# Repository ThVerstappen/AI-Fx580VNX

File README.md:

# AI-Fx580VNX

Bo mạch thay thế cho Casio fx-580VN X (ESP32-S3, TCA8418, e-paper 2,13", USB-C, pin LiPo). Đây là phần hoàn thiện nhất: **V8 USB_FIX1** (11/10/2026).

- `Hardware/FX580_Main_EPD_LAYOUT_V8/` — project KiCad 10.0.5 (sch/pcb/lib local, BOM/CPL, báo cáo ERC/DRC/CAM). Đọc `USB_FIX1_REPORTS/REVIEW_USB_FIX1.md` trước.
- `GOI_GERBER_FX580_V8_USB_FIX1_5PCB/` — Gerber/Excellon cho 5 PCB trống.
- `GOI_LAP_6_LINH_KIEN_FX580_V8_USB_FIX1_2BO/` — BOM/CPL lắp 6 linh kiện.
- `GOI_STENCIL_FX580_V8_USB_FIX1_65PARTS/` — stencil 65 linh kiện còn lại.
- `HUONG_DAN_SETUP_MURATA_FX580_V8/` — hướng dẫn đặt PCB/stencil.

Giới hạn: ERC/DRC = 0 nhưng chưa thử USB/ESD trên bo thật; toàn tuyến 90 Ω chưa được chứng minh. Chưa có firmware hoàn chỉnh. Các phiên bản V2–V7, trial và dữ liệu trung gian không đưa lên.

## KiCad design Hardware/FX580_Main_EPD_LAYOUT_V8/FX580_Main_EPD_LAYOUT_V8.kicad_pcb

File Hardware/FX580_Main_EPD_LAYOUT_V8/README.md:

# FX580 V8 USB_FIX1 — project hiện hành

Revision mới nhất hoàn tất ngày 11/10/2026. Mở **FX580_Main_EPD_LAYOUT_V8.kicad_pro** bằng KiCad 10.0.5; PCB và schematic cùng tên. Thư viện local dùng `${KIPRJMOD}/lib`.

Đã sửa routing D−/D+, cải thiện GND tham chiếu và thêm tụ C25 gần U6. ERC/DRC/unconnected/parity đều 0 theo rules hiện hành. CAM độc lập xác nhận 263 lỗ/slot, pad và 100 miền tiếp điểm của 50 phím. Chi tiết và giới hạn tại **USB_FIX1_REPORTS/REVIEW_USB_FIX1.md**; toàn tuyến 90 Ω và thử USB/ESD trên bo thật vẫn cần xác nhận.

BOM/CPL hiện hành: `assembly/BOM_JLCPCB_V8_USB_FIX1.csv` và `assembly/CPL_JLCPCB_V8_USB_FIX1.csv`, 35 nhóm / 71 linh kiện mỗi bo. `assembly/inherited_v7/` giữ chứng cứ vị trí/góc/cực của linh kiện không đổi; BOM V7 không bao gồm C25.

Gói Gerber mới trong workspace: `GOI_GERBER_FX580_V8_USB_FIX1_5PCB/FX580_V8_USB_FIX1_GERBER.zip`. Phạm vi 5 PCB trống / 0 PCBA / không stencil. Upload/quote JLCONE cũ chưa được thay trong lượt này.

V7 BOOST2 và V8 ngày 08/10 được giữ làm lịch sử. Project trước sửa nằm trong `usb_fix_20261010/V8_BEFORE_USB_FIX1.zip`; assembly cũ tại `usb_fix_20261010/assembly_before_usb/`. Ba file CAD ở root là bản hiện hành; `MANIFEST_SHA256.json` ghi hash các file giao. Bản ZIP project có đủ thư viện, BOM/CPL và báo cáo, không gồm các candidate/trial.

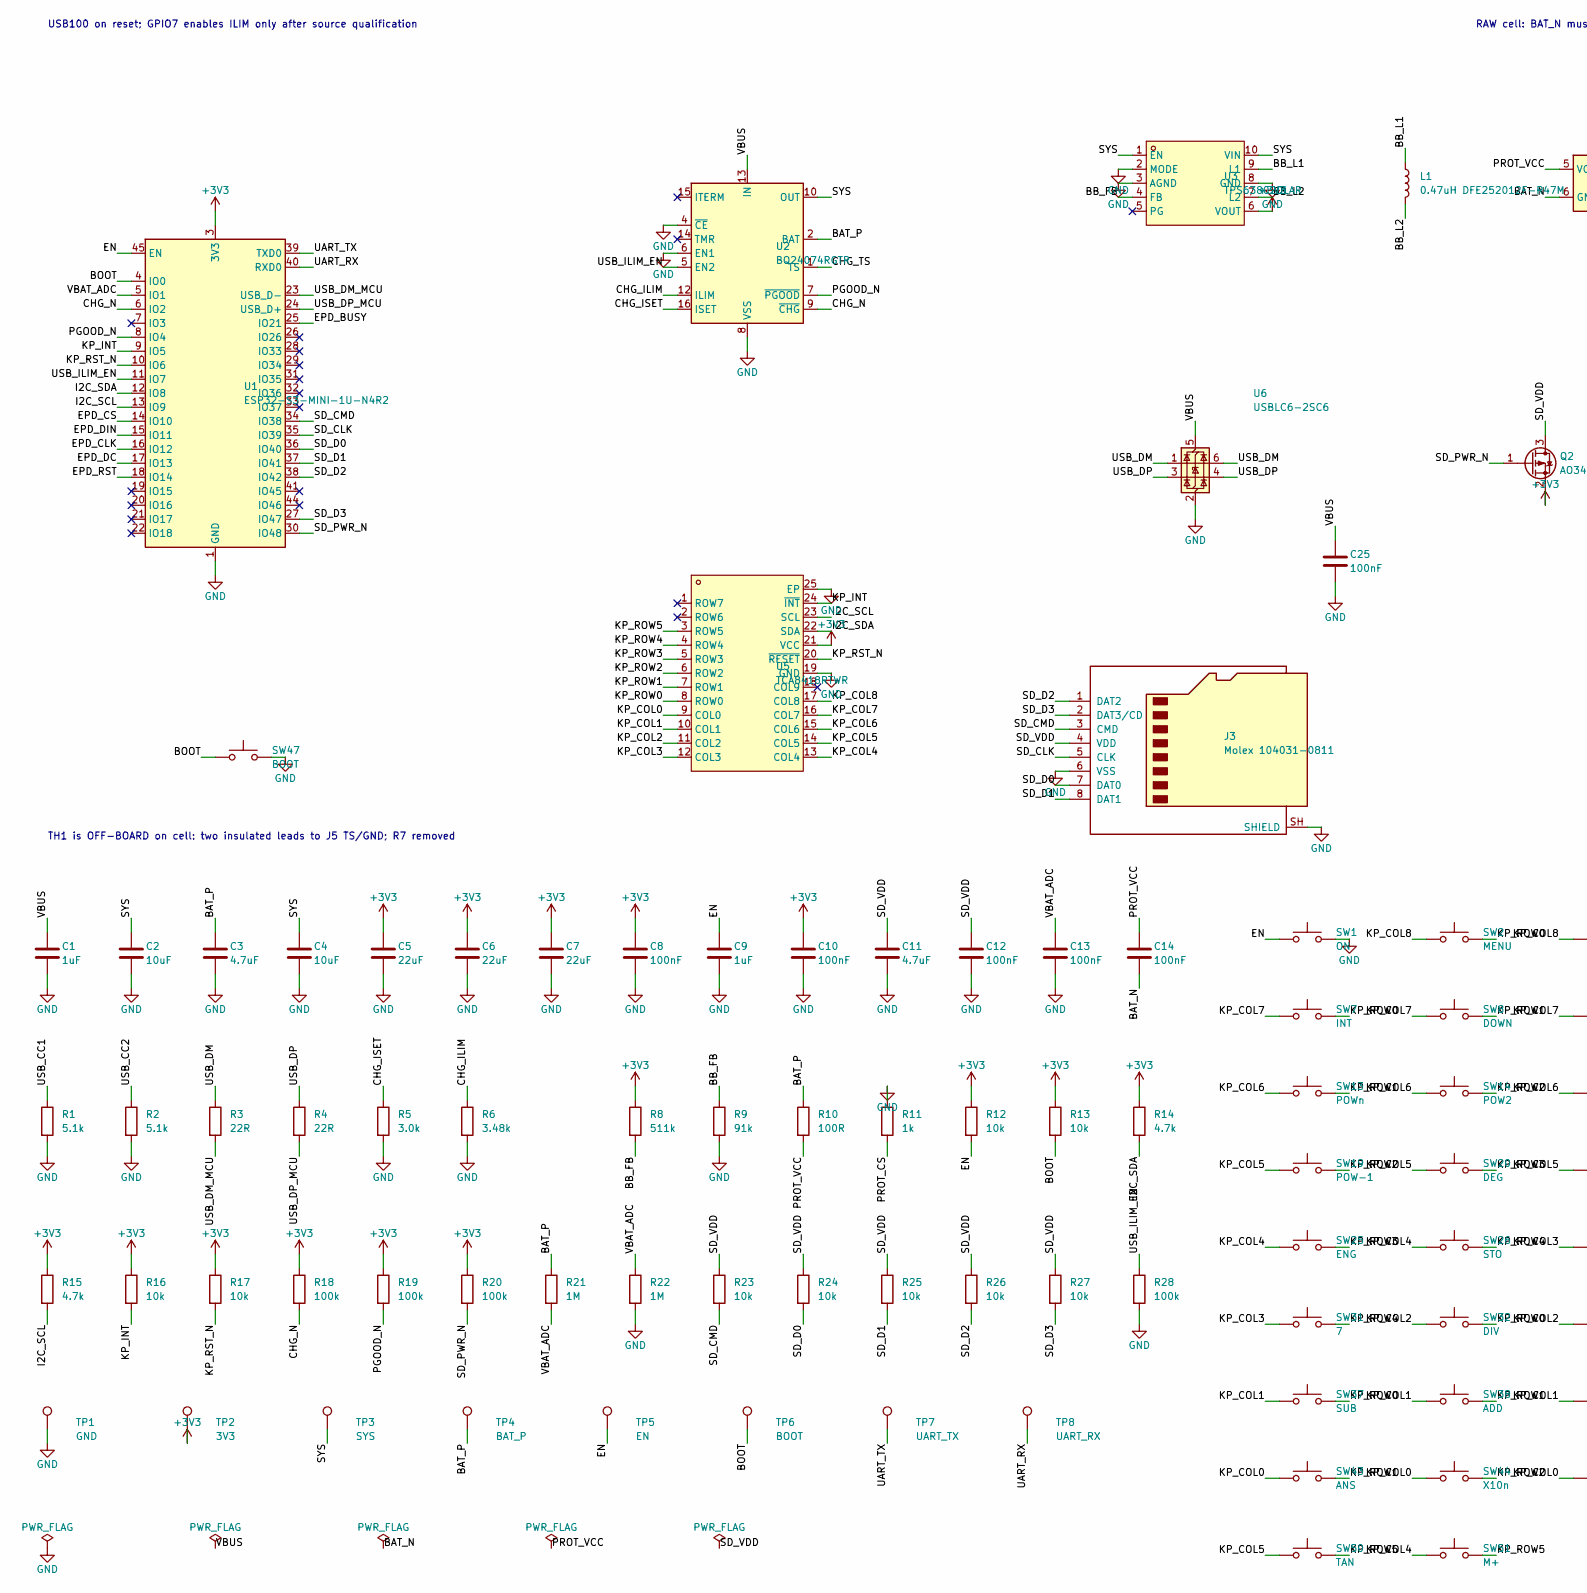
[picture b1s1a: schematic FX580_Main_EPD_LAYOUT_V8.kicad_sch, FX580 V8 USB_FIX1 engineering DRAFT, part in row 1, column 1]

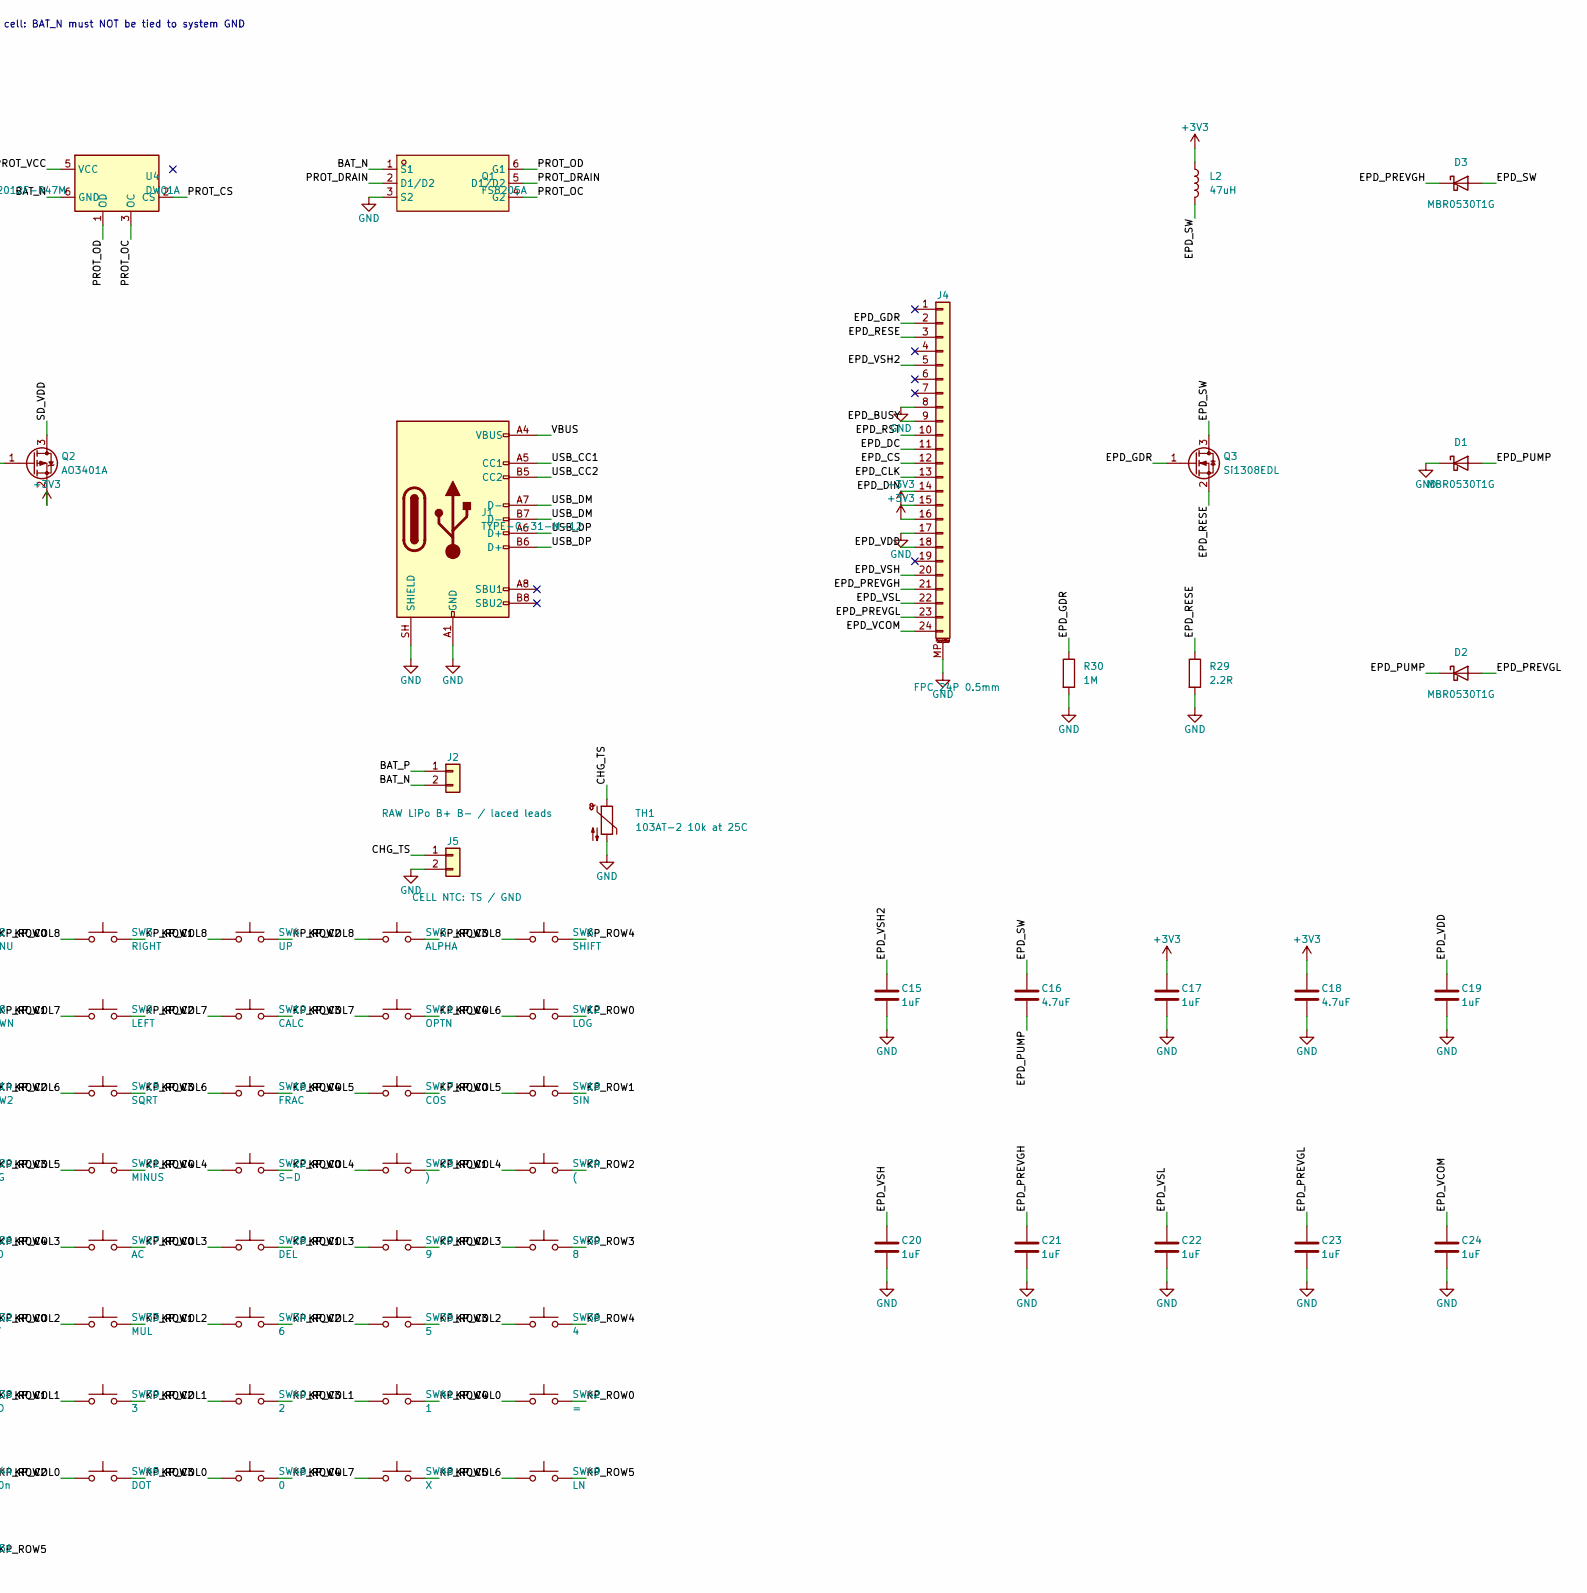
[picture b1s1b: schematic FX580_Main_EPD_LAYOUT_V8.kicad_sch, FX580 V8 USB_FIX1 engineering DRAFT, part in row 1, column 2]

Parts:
C1, C9: 1uF; C_0603_1608Metric; Voltage 50V; LCSC C15849
C2, C4: 10uF; C_0805_2012Metric; Voltage 10V; LCSC C5137471
C3, C11: 4.7uF; C_0603_1608Metric; Voltage 16V; LCSC C19666
C5, C6, C7: 22uF; C_0805_2012Metric; Voltage 10V; LCSC C22367831
C8, C10, C12, C13, C14, C25: 100nF; C_0603_1608Metric; Voltage 50V; LCSC C14663
C15, C17, C19, C20, C21, C22, C23, C24: 1uF; C_0603_1608Metric; Voltage 50V
C16, C18: 4.7uF; C_0805_2012Metric; Voltage 50V
D1, D2, D3: MBR0530T1G; D_SOD-123; MPN MBR0530T1G; LCSC C82046
J1: TYPE-C-31-M-12; USB_C_Receptacle_HRO_TYPE-C-31-M-12; MPN TYPE-C-31-M-12
J2: RAW LiPo B+ B- / laced leads; Battery_Pads_Reinforced
J3: Molex 104031-0811; microSD_HC_Molex_104031-0811; LCSC C585350
J4: FPC 24P 0.5mm; Hirose_FH12-24S-0.5SH_1x24-1MP_P0.50mm_Horizontal; MPN FH12-24S-0.5SH(55)
J5: CELL NTC: TS / GND; Cell_NTC_Pads
L1: 0.47uH DFE252012F-R47M; DFE252012F; LCSC C703140
L2: 47uH; L_TDK_BCL322515RT; MPN BCL322515RT-470M-D; LCSC C3220812
Q1: FS8205A; SOT-23-6_L2.9-W1.6-P0.95-LS2.8-BR; LCSC C2830320
Q2: AO3401A; SOT-23; LCSC C15127
Q3: Si1308EDL; SOT-323_SC-70
R1, R2: 5.1k; R_0603_1608Metric; Tolerance 1%; LCSC C23186
R3, R4: 22R; R_0603_1608Metric; Tolerance 1%; LCSC C23345
R5: 3.0k; R_0603_1608Metric; Tolerance 1%; LCSC C4211
R6: 3.48k; R_0603_1608Metric; Tolerance 1%; LCSC C22996
R8: 511k; R_0603_1608Metric; Tolerance 1%; LCSC C23194
R9: 91k; R_0603_1608Metric; Tolerance 1%; LCSC C23265
R10: 100R; R_0603_1608Metric; Tolerance 1%; LCSC C22775
R11: 1k; R_0603_1608Metric; Tolerance 1%; LCSC C21190
R12, R13, R16, R17, R23, R24, R25, R26, R27: 10k; R_0603_1608Metric; Tolerance 1%; LCSC C2906982
R14, R15: 4.7k; R_0603_1608Metric; Tolerance 1%; LCSC C23162
R18, R19, R20, R28: 100k; R_0603_1608Metric; Tolerance 1%; LCSC C25803
R21, R22: 1M; R_0603_1608Metric; Tolerance 1%; LCSC C22935
R29: 2.2R; R_0603_1608Metric; Tolerance 1%
R30: 1M; R_0603_1608Metric
SW1: ON; Keypad_Interleaved_5p2
SW2: MENU; Keypad_Interleaved_5p2
SW3: RIGHT; Keypad_Interleaved_5p2
SW4: UP; Keypad_Interleaved_5p2
SW5: ALPHA; Keypad_Interleaved_5p2
SW6: SHIFT; Keypad_Interleaved_5p2
SW7: INT; Keypad_Interleaved_5p2
SW8: DOWN; Keypad_Interleaved_5p2
SW9: LEFT; Keypad_Interleaved_5p2
SW10: CALC; Keypad_Interleaved_5p2
SW11: OPTN; Keypad_Interleaved_5p2
SW12: LOG; Keypad_Interleaved_5p2
SW13: POWn; Keypad_Interleaved_5p2
SW14: POW2; Keypad_Interleaved_5p2
SW15: SQRT; Keypad_Interleaved_5p2
SW16: FRAC; Keypad_Interleaved_5p2
SW17: COS; Keypad_Interleaved_5p2
SW18: SIN; Keypad_Interleaved_5p2
SW19: POW-1; Keypad_Interleaved_5p2
SW20: DEG; Keypad_Interleaved_5p2
SW21: MINUS; Keypad_Interleaved_5p2
SW22: S-D; Keypad_Interleaved_5p2
SW23: ); Keypad_Interleaved_5p2
SW24: (; Keypad_Interleaved_5p2
SW25: ENG; Keypad_Interleaved_5p2
SW26: STO; Keypad_Interleaved_5p2
SW27: AC; Keypad_Interleaved_5p2
SW28: DEL; Keypad_Interleaved_5p2
SW29: 9; Keypad_Interleaved_5p2
SW30: 8; Keypad_Interleaved_5p2
SW31: 7; Keypad_Interleaved_5p2
SW32: DIV; Keypad_Interleaved_5p2
SW33: MUL; Keypad_Interleaved_5p2
SW34: 6; Keypad_Interleaved_5p2
SW35: 5; Keypad_Interleaved_5p2
SW36: 4; Keypad_Interleaved_5p2
SW37: SUB; Keypad_Interleaved_5p2
SW38: ADD; Keypad_Interleaved_5p2
SW39: 3; Keypad_Interleaved_5p2
SW40: 2; Keypad_Interleaved_5p2
SW41: 1; Keypad_Interleaved_5p2
SW42: =; Keypad_Interleaved_5p2
SW43: ANS; Keypad_Interleaved_5p2
SW44: X10n; Keypad_Interleaved_5p2
SW45: DOT; Keypad_Interleaved_5p2
SW46: 0; Keypad_Interleaved_5p2
SW47: BOOT; Boot_Pads
SW48: X; Keypad_Interleaved_5p2
SW49: LN; Keypad_Interleaved_5p2
SW50: TAN; Keypad_Interleaved_5p2
SW51: M+; Keypad_Interleaved_5p2
TH1: 103AT-2 10k at 25C
TP1: GND; TestPoint_Pad_D1.0mm
TP2: 3V3; TestPoint_Pad_D1.0mm
TP3: SYS; TestPoint_Pad_D1.0mm
TP4: BAT_P; TestPoint_Pad_D1.0mm
TP5: EN; TestPoint_Pad_D1.0mm
TP6: BOOT; TestPoint_Pad_D1.0mm
TP7: UART_TX; TestPoint_Pad_D1.0mm
TP8: UART_RX; TestPoint_Pad_D1.0mm
U1: ESP32-S3-MINI-1U-N4R2; ESP32-S3-MINI-1U; MPN ESP32-S3-MINI-1U-N4R2
U2: BQ24074RGTR; BQ24074_V6; LCSC C54313
U3: TPS63802DLAR; VSON-10_L3.0-W2.0-P0.50-TL; LCSC C2845237
U4: DW01A; SOT-23-6; LCSC C351410
U5: TCA8418RTWR; WQFN-24_L4.0-W4.0-P0.50-TL-EP2.5; LCSC C138713
U6: USBLC6-2SC6; SOT-23-6; LCSC C7519

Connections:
+3V3: C5.1, C6.1, C7.1, C8.1, C10.1, C17.1, C18.1, J4.15, J4.16, L2.1, Q2.2 (S), R8.1, R12.1, R13.1, R14.1, R15.1, R16.1, R17.1, R18.1, R19.1, R20.1, TP2.1, U1.3 (3V3), U3.6 (VOUT), U5.21 (VCC)
/BAT_N: C14.2, J2.2, Q1.1 (S1), U4.6 (GND)
/BAT_P: C3.1, J2.1, R10.1, R21.1, TP4.1, U2.2 (BAT), U2.3 (BAT)
/BB_FB: R8.2, R9.1, U3.4 (FB)
/BB_L1: L1.1, U3.9 (L1)
/BB_L2: L1.2, U3.7 (L2)
/BOOT: R13.2, SW47.1, TP6.1, U1.4 (IO0)
/CHG_ILIM: R6.1, U2.12 (ILIM)
/CHG_ISET: R5.1, U2.16 (ISET)
/CHG_N: R18.2, U1.6 (IO2), U2.9 (~CHG)
/CHG_TS: J5.1, TH1.1, U2.1 (TS)
/EN: C9.1, R12.2, SW1.1, TP5.1, U1.45 (EN)
/EPD_BUSY: J4.9, U1.25 (IO21)
/EPD_CLK: J4.13, U1.16 (IO12)
/EPD_CS: J4.12, U1.14 (IO10)
/EPD_DC: J4.11, U1.17 (IO13)
/EPD_DIN: J4.14, U1.15 (IO11)
/EPD_GDR: J4.2, Q3.1 (G), R30.1
/EPD_PREVGH: C21.1, D3.1 (K), J4.21
/EPD_PREVGL: C23.1, D2.2 (A), J4.23
/EPD_PUMP: C16.2, D1.2 (A), D2.1 (K)
/EPD_RESE: J4.3, Q3.2 (S), R29.1
/EPD_RST: J4.10, U1.18 (IO14)
/EPD_SW: C16.1, D3.2 (A), L2.2, Q3.3 (D)
/EPD_VCOM: C24.1, J4.24
/EPD_VDD: C19.1, J4.18
/EPD_VSH: C20.1, J4.20
/EPD_VSH2: C15.1, J4.5
/EPD_VSL: C22.1, J4.22
/I2C_SCL: R15.2, U1.13 (IO9), U5.23 (SCL)
/I2C_SDA: R14.2, U1.12 (IO8), U5.22 (SDA)
/KP_COL0: SW42.1, SW43.1, SW44.1, SW45.1, SW46.1, U5.9 (COL0)
/KP_COL1: SW37.1, SW38.1, SW39.1, SW40.1, SW41.1, U5.10 (COL1)
/KP_COL2: SW32.1, SW33.1, SW34.1, SW35.1, SW36.1, U5.11 (COL2)
/KP_COL3: SW27.1, SW28.1, SW29.1, SW30.1, SW31.1, U5.12 (COL3)
/KP_COL4: SW22.1, SW23.1, SW24.1, SW25.1, SW26.1, SW51.1, U5.13 (COL4)
/KP_COL5: SW17.1, SW18.1, SW19.1, SW20.1, SW21.1, SW50.1, U5.14 (COL5)
/KP_COL6: SW12.1, SW13.1, SW14.1, SW15.1, SW16.1, SW49.1, U5.15 (COL6)
/KP_COL7: SW7.1, SW8.1, SW9.1, SW10.1, SW11.1, SW48.1, U5.16 (COL7)
/KP_COL8: SW2.1, SW3.1, SW4.1, SW5.1, SW6.1, U5.17 (COL8)
/KP_INT: R16.2, U1.9 (IO5), U5.24 (~INT)
/KP_ROW0: SW2.2, SW7.2, SW12.2, SW17.2, SW22.2, SW27.2, SW32.2, SW37.2, SW42.2, U5.8 (ROW0)
/KP_ROW1: SW3.2, SW8.2, SW13.2, SW18.2, SW23.2, SW28.2, SW33.2, SW38.2, SW43.2, U5.7 (ROW1)
/KP_ROW2: SW4.2, SW9.2, SW14.2, SW19.2, SW24.2, SW29.2, SW34.2, SW39.2, SW44.2, U5.6 (ROW2)
/KP_ROW3: SW5.2, SW10.2, SW15.2, SW20.2, SW25.2, SW30.2, SW35.2, SW40.2, SW45.2, U5.5 (ROW3)
/KP_ROW4: SW6.2, SW11.2, SW16.2, SW21.2, SW26.2, SW31.2, SW36.2, SW41.2, SW46.2, U5.4 (ROW4)
/KP_ROW5: SW48.2, SW49.2, SW50.2, SW51.2, U5.3 (ROW5)
/KP_RST_N: R17.2, U1.10 (IO6), U5.20 (~RESET)
/PGOOD_N: R19.2, U1.8 (IO4), U2.7 (~PGOOD)
/PROT_CS: R11.2, U4.2 (CS)
/PROT_DRAIN: Q1.2 (D1/D2), Q1.5 (D1/D2)
/PROT_OC: Q1.4 (G2), U4.3 (OC)
/PROT_OD: Q1.6 (G1), U4.1 (OD)
/PROT_VCC: C14.1, R10.2, U4.5 (VCC)
/SD_CLK: J3.5 (CLK), U1.35 (IO39)
/SD_CMD: J3.3 (CMD), R23.2, U1.34 (IO38)
/SD_D0: J3.7 (DAT0), R24.2, U1.36 (IO40)
/SD_D1: J3.8 (DAT1), R25.2, U1.37 (IO41)
/SD_D2: J3.1 (DAT2), R26.2, U1.38 (IO42)
/SD_D3: J3.2 (DAT3/CD), R27.2, U1.27 (IO47)
/SD_PWR_N: Q2.1 (G), R20.2, U1.30 (IO48)
/SD_VDD: C11.1, C12.1, J3.4 (VDD), Q2.3 (D), R23.1, R24.1, R25.1, R26.1, R27.1
/SYS: C2.1, C4.1, TP3.1, U2.10 (OUT), U2.11 (OUT), U3.1 (EN), U3.10 (VIN)
/UART_RX: TP8.1, U1.40 (RXD0)
/UART_TX: TP7.1, U1.39 (TXD0)
/USB_CC1: J1.A5 (CC1), R1.1
/USB_CC2: J1.B5 (CC2), R2.1
/USB_DM: J1.A7 (D-), J1.B7 (D-), R3.1, U6.1 (I/O1), U6.6 (I/O1)
/USB_DM_MCU: R3.2, U1.23 (USB_D-)
/USB_DP: J1.A6 (D+), J1.B6 (D+), R4.1, U6.3 (I/O2), U6.4 (I/O2)
/USB_DP_MCU: R4.2, U1.24 (USB_D+)
/USB_ILIM_EN: R28.1, U1.11 (IO7), U2.5 (EN2)
/VBAT_ADC: C13.1, R21.2, R22.1, U1.5 (IO1)
/VBUS: C1.1, C25.1, J1.A4 (VBUS), J1.A9 (VBUS), J1.B4 (VBUS), J1.B9 (VBUS), U2.13 (IN), U6.5 (VBUS)
GND: C1.2, C2.2, C3.2, C4.2, C5.2, C6.2, C7.2, C8.2, C9.2, C10.2, C11.2, C12.2, C13.2, C15.2, C17.2, C18.2, C19.2, C20.2, C21.2, C22.2, C23.2, C24.2, C25.2, D1.1 (K), J1.A1 (GND), J1.A12 (GND), J1.B1 (GND), J1.B12 (GND), J1.SH (SHIELD), J3.6 (VSS), J3.SH (SHIELD), J4.8, J4.17, J4.MP (MountPin), J5.2, Q1.3 (S2), R1.2, R2.2, R5.2, R6.2, R9.2, R11.1, R22.2, R28.2, R29.2, R30.2, SW1.2, SW47.2, TH1.2, TP1.1, U1.1 (GND), U1.2 (GND), U1.42 (GND), U1.43 (GND), U1.46 (GND), U1.47 (GND), U1.48 (GND), U1.49 (GND), U1.50 (GND), U1.51 (GND), U1.52 (GND), U1.53 (GND), U1.54 (GND), U1.55 (GND), U1.56 (GND), U1.57 (GND), U1.58 (GND), U1.59 (GND), U1.60 (GND), U1.61 (GND), U1.62 (GND), U1.63 (GND), U1.64 (GND), U1.65 (GND), U2.4 (~CE), U2.6 (EN1), U2.8 (VSS), U2.17 (VSS), U3.2 (MODE), U3.3 (AGND), U3.8 (GND), U5.19 (GND), U5.25 (EP), U6.2 (GND)

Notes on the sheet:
USB100 on reset; GPIO7 enables ILIM only after source qualification
RAW cell: BAT_N must NOT be tied to system GND
TH1 is OFF-BOARD on cell: two insulated leads to J5 TS/GND; R7 removed

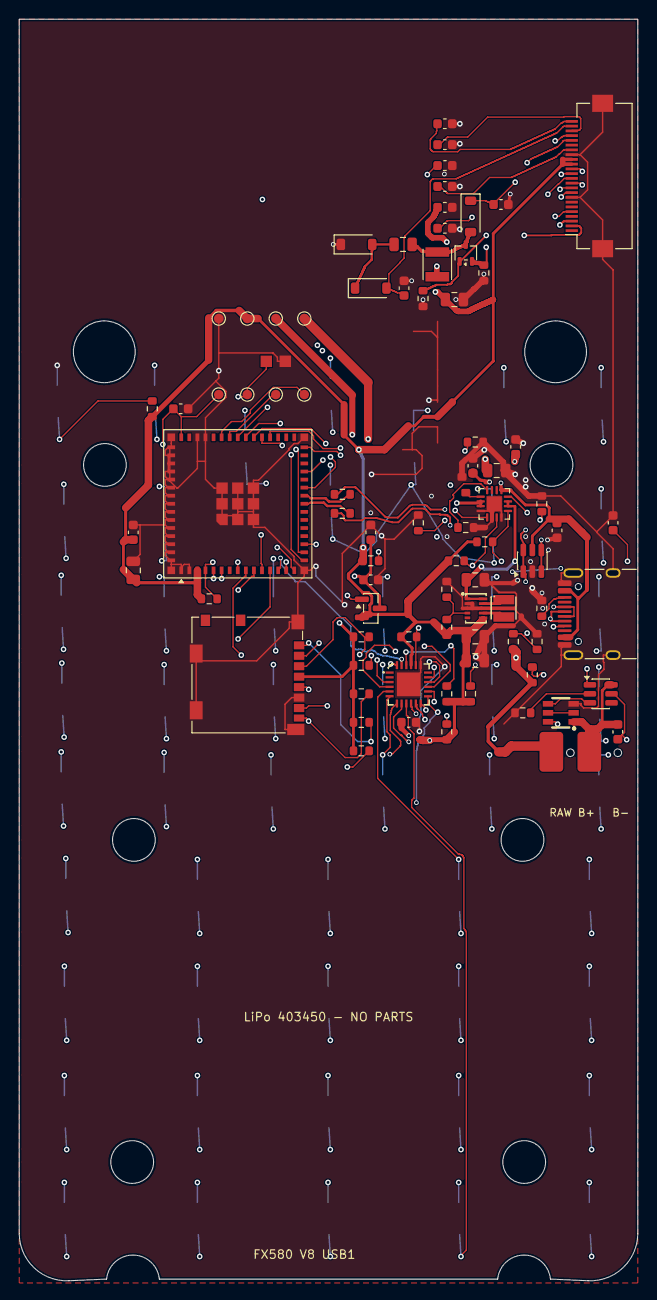
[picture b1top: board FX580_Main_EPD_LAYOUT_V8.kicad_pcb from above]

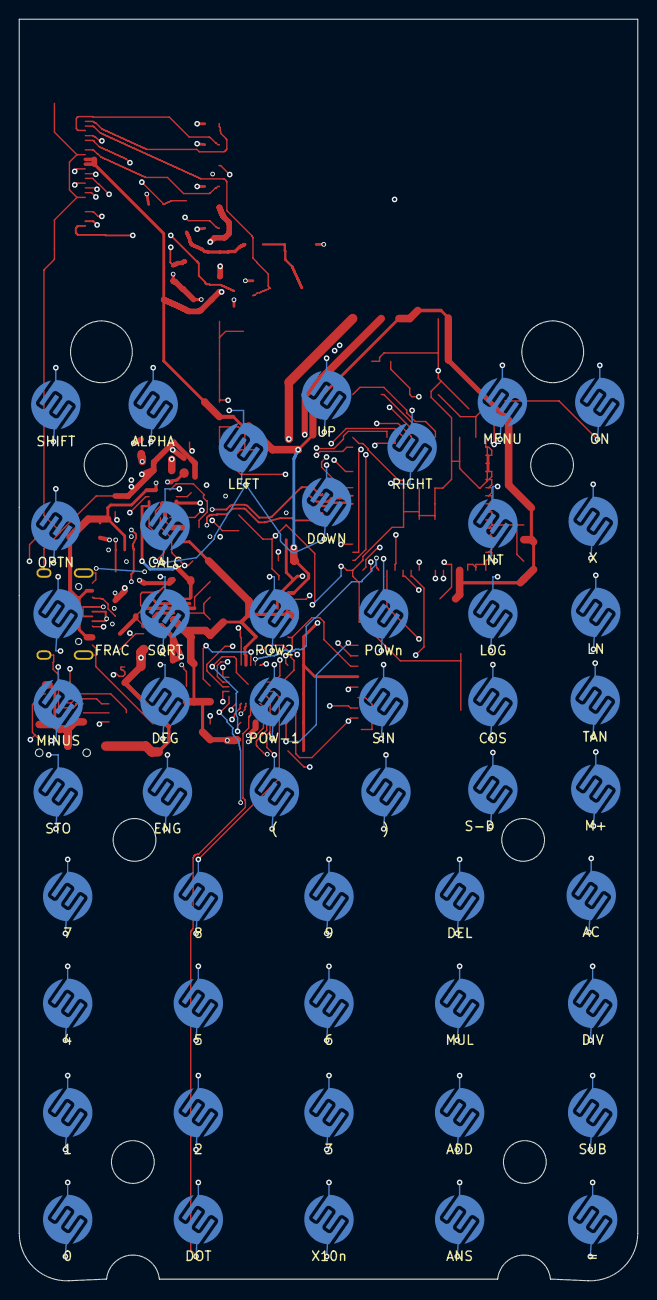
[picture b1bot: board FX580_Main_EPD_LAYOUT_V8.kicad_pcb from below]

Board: 4 copper layers, 65.1 x 132.8 mm, 132 parts (50 on the bottom side), 75 nets.

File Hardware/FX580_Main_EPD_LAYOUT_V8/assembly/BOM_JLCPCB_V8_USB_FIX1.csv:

Comment,Designator,Footprint,LCSCPart#,Manufacturer Part Number,Manufacturer,Quantity
1uF 50V 10% X5R,"C1,C9",Capacitor_SMD:C_0603_1608Metric,C15849,CL10A105KB8NNNC,Samsung Electro-Mechanics,2
10uF 10V 10% X5R,"C2,C4",Capacitor_SMD:C_0805_2012Metric,C5137471,FCC0805X106K100FT,FOJAN,2
4.7uF 16V 10% X5R,"C3,C11",Capacitor_SMD:C_0603_1608Metric,C19666,CL10A475KO8NNNC,Samsung Electro-Mechanics,2
22uF 10V 20% X5R,"C5,C6,C7",Capacitor_SMD:C_0805_2012Metric,C22367831,HGC0805R5226M100NSLJ,Chinocera,3
100nF 50V 10% X7R,"C8,C10,C12,C13,C14,C25",Capacitor_SMD:C_0603_1608Metric,C14663,CC0603KRX7R9BB104,YAGEO,6
1uF 50V 10% X7R,"C15,C17,C19,C20,C21,C22,C23,C24",Capacitor_SMD:C_0603_1608Metric,C559769,CC0603KRX7R9BB105,YAGEO,8
4.7uF 50V 10% X5R,"C16,C18",Capacitor_SMD:C_0805_2012Metric,C98192,CL21A475KBQNNNE,Samsung Electro-Mechanics,2
MBR0530T1G 30V 0.5A Vf<=0.43V@0.5A,"D1,D2,D3",Diode_SMD:D_SOD-123,C82046,MBR0530T1G,onsemi,3
TYPE-C-31-M-12,J1,FX580:USB_C_Receptacle_HRO_TYPE-C-31-M-12,C165948,TYPE-C-31-M-12,Korean Hroparts Elec,1
Molex 104031-0811,J3,Connector_Card:microSD_HC_Molex_104031-0811,C585350,1040310811,MOLEX,1
FPC 24P 0.5mm,J4,Connector_FFC-FPC:Hirose_FH12-24S-0.5SH_1x24-1MP_P0.50mm_Horizontal,C202112,FH12-24S-0.5SH(55),HRS(Hirose),1
0.47uH DFE252012F-R47M,L1,FX580:DFE252012F,C703140,DFE252012F-R47M=P2,Murata Electronics,1
47uH 20% rated 0.57A H1.5mm,L2,FX580:L_TDK_BCL322515RT,C3220812,BCL322515RT-470M-D,TDK,1
FS8205A,Q1,FX580:SOT-23-6_L2.9-W1.6-P0.95-LS2.8-BR,C2830320,FS8205A,TECH PUBLIC,1
AO3401A,Q2,Package_TO_SOT_SMD:SOT-23,C15127,AO3401A,Alpha & Omega Semicon,1
Si1308EDL,Q3,Package_TO_SOT_SMD:SOT-323_SC-70,C469327,SI1308EDL-T1-GE3,Vishay Intertech,1
5.1k 1%,"R1,R2",Resistor_SMD:R_0603_1608Metric,C23186,0603WAF5101T5E,UNI-ROYAL(Uniroyal Elec),2
22R 1%,"R3,R4",Resistor_SMD:R_0603_1608Metric,C23345,0603WAF220JT5E,UNI-ROYAL(Uniroyal Elec),2
3.0k 1%,R5,Resistor_SMD:R_0603_1608Metric,C4211,0603WAF3001T5E,UNI-ROYAL(Uniroyal Elec),1
3.48k 1%,R6,Resistor_SMD:R_0603_1608Metric,C22996,0603WAF3481T5E,UNI-ROYAL(Uniroyal Elec),1
511k 1%,R8,Resistor_SMD:R_0603_1608Metric,C23194,0603WAF5113T5E,UNI-ROYAL(Uniroyal Elec),1
91k 1%,R9,Resistor_SMD:R_0603_1608Metric,C23265,0603WAF9102T5E,UNI-ROYAL(Uniroyal Elec),1
100R 1%,R10,Resistor_SMD:R_0603_1608Metric,C22775,0603WAF1000T5E,UNI-ROYAL(Uniroyal Elec),1
1k 1%,R11,Resistor_SMD:R_0603_1608Metric,C21190,0603WAF1001T5E,UNI-ROYAL(Uniroyal Elec),1
10k 1%,"R12,R13,R16,R17,R23,R24,R25,R26,R27",Resistor_SMD:R_0603_1608Metric,C2906982,FRC0603F1002TS,FOJAN,9
4.7k 1%,"R14,R15",Resistor_SMD:R_0603_1608Metric,C23162,0603WAF4701T5E,UNI-ROYAL(Uniroyal Elec),2
100k 1%,"R18,R19,R20,R28",Resistor_SMD:R_0603_1608Metric,C25803,0603WAF1003T5E,UNI-ROYAL(Uniroyal Elec),4
1M 1%,"R21,R22,R30",Resistor_SMD:R_0603_1608Metric,C22935,0603WAF1004T5E,UNI-ROYAL(Uniroyal Elec),3
2.2R 1%,R29,Resistor_SMD:R_0603_1608Metric,C22939,0603WAF220KT5E,UNI-ROYAL(Uniroyal Elec),1
ESP32-S3-MINI-1U-N4R2,U1,FX580:ESP32-S3-MINI-1U,C22356044,ESP32-S3-MINI-1U-N4R2,Espressif Systems,1
BQ24074RGTR,U2,FX580:BQ24074_V6,C54313,BQ24074RGTR,Texas Instruments,1
TPS63802DLAR,U3,FX580:VSON-10_L3.0-W2.0-P0.50-TL,C2845237,TPS63802DLAR,Texas Instruments,1
DW01A,U4,Package_TO_SOT_SMD:SOT-23-6,C351410,DW01A,PUOLOP,1
TCA8418RTWR,U5,FX580:WQFN-24_L4.0-W4.0-P0.50-TL-EP2.5,C138713,TCA8418RTWR,Texas Instruments,1
USBLC6-2SC6,U6,Package_TO_SOT_SMD:SOT-23-6,C7519,USBLC6-2SC6,STMicroelectronics,1
